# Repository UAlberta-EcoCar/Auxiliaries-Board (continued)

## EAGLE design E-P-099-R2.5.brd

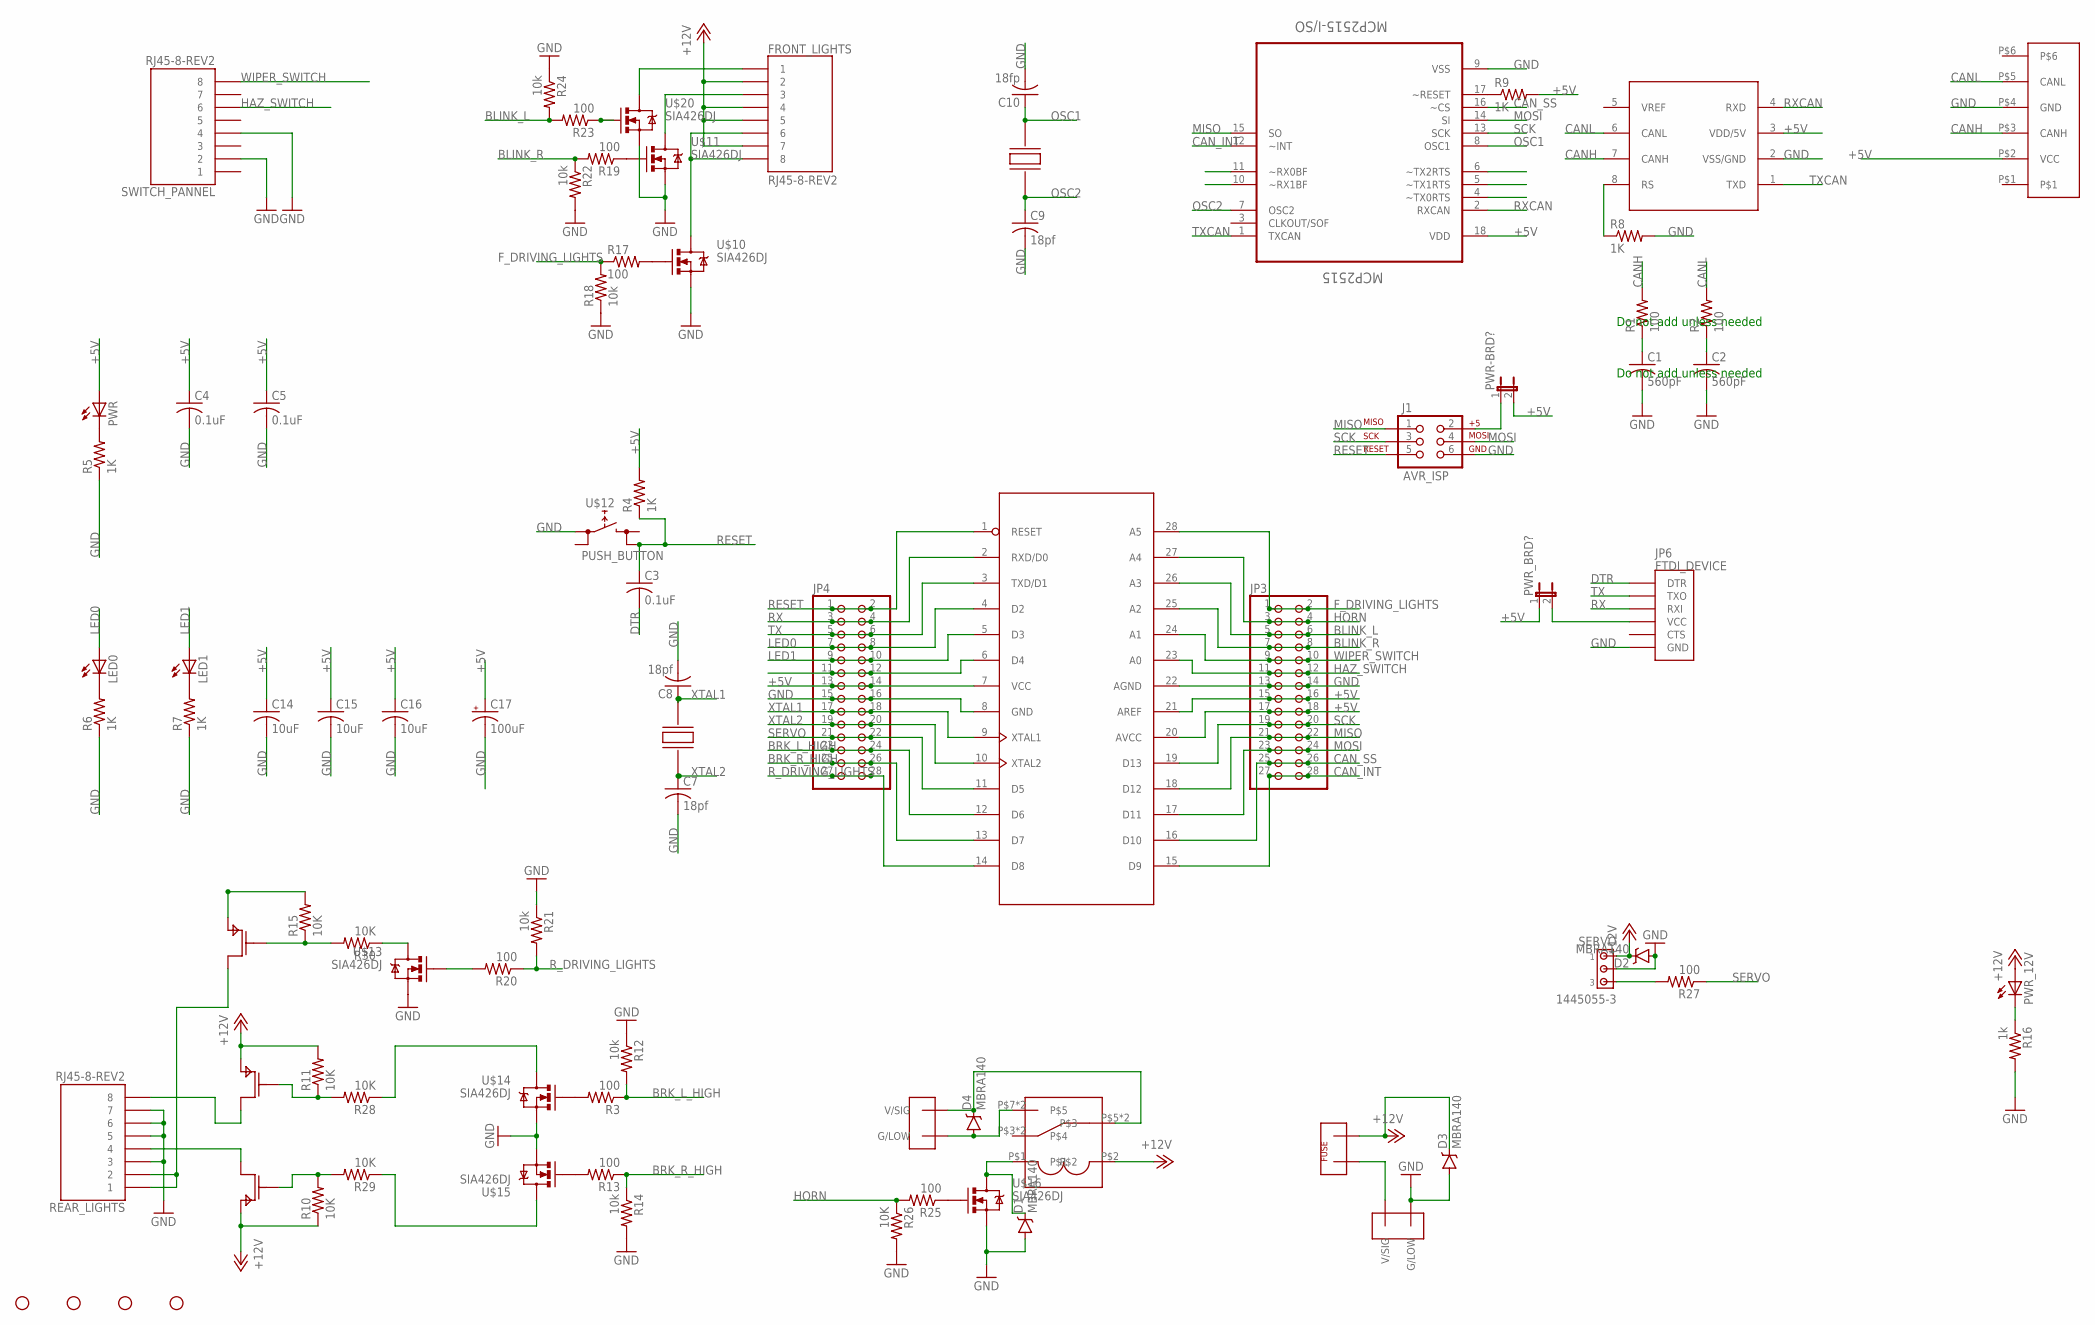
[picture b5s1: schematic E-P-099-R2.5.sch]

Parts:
C1, C2: 560pF; C0805
C3, C4, C5: 0.1uF; C0805
C7, C8, C9: 18pf; C0805
C10: 18fp; C0805
C14, C15, C16: 10uF; C0805
C17: 100uF; PANASONIC_D
CAN-BUS: CAN_6P6C
D1, D2, D3, D4: MBRA140; SMA-DIODE
FRONT_LIGHTS: RJ45-8-REV2; RJ45-8
HORN: TE770966; 2X1-MATE-N-LOCK
J1: AVR_ISP; 2X3
JP3, JP4: PINHD-2X14; 2X14
JP6: FTDI_DEVICE; FTDI_DEVICE_SIDE
LED0, LED1: LED1206; LED-1206
MCP2515: MCP2515-I/SO; SOIC127P1034X264-18N
PWR: LED1206; LED-1206
PWR-BRD?: JP1E; JP1
PWR_12V: LEDCHIPLED_1206; CHIPLED_1206
PWR_BRD?: JP1E; JP1
R1, R2, R3, R13, R17, R19, R20, R23, R25, R27: 100; M0805
R4, R5, R6, R7, R8, R9: 1K; M0805
R10, R11, R15, R26, R28, R29, R30: 10K; M0805
R12, R14, R18, R21, R22, R24: 10k; M0805
R16: 1k; M0805
REAR_LIGHTS: RJ45-8-REV2; RJ45-8
SERVO: 1445055-3
STANDOFF1, STANDOFF2, STANDOFF3, STANDOFF4: STAND-OFF
SWITCH_PANNEL: RJ45-8-REV2; RJ45-8
U$2: MCP2551DIP; DIP8
U$3, U$5, U$6: SIA449DJ; SIA449DJ-T1-GE3CT-ND
U$4: ATMEGA328; DIP28-0.3IN
U$7: RELAY; RTD34012
U$8: TE770966; 2X1-MATE-N-LOCK
U$9: FUSEMINI-BLADE; MINI-BLADE-FUSE
U$10, U$11, U$13, U$14, U$15, U$16, U$20: SIA426DJ; SC70-6L
U$12: PUSH_BUTTON; PUSHBUTTON
U$18, U$19: CRYSTAL; 7A_CRYSTAL

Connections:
+5V: C4.1, C5.1, C14.1, C15.1, C16.1, C17.+, CAN-BUS.P$2 (VCC), JP3.15, JP3.16, JP3.17, JP3.18, JP4.13, JP4.14, MCP2515.18 (VDD), PWR.A, PWR-BRD?.2, PWR_BRD?.1, R4.2, R9.2, U$2.3 (VDD/5V), U$4.7 (VCC), U$4.20 (AVCC), U$4.21 (AREF)
+12V: D2.C, D3.C, FRONT_LIGHTS.2, FRONT_LIGHTS.4, FRONT_LIGHTS.5, FRONT_LIGHTS.7, PWR_12V.A, R10.1, R11.2, R15.2, SERVO.1, U$3.P$4 (P$S), U$3.P$5 (P$S), U$5.P$4 (P$S), U$5.P$5 (P$S), U$6.P$4 (P$S), U$6.P$5 (P$S), U$7.P$2, U$9.OUT
BLINK_L: JP3.5, JP3.6, R23.2, R24.2, U$4.26 (A3)
BLINK_R: JP3.7, JP3.8, R19.2, R22.1, U$4.25 (A2)
BRK_L_HIGH: JP4.23, JP4.24, R3.1, R12.2, U$4.12 (D6)
BRK_R_HIGH: JP4.25, JP4.26, R13.1, R14.1, U$4.13 (D7)
CANH: CAN-BUS.P$3 (CANH), R1.2, U$2.7 (CANH)
CANL: CAN-BUS.P$5 (CANL), R2.2, U$2.6 (CANL)
CAN_INT: JP3.27, JP3.28, MCP2515.12 (~INT), U$4.15 (D9)
CAN_SS: JP3.25, JP3.26, MCP2515.16 (~CS), U$4.16 (D10)
DTR: C3.2, JP6.P$1 (DTR)
F_DRIVING_LIGHTS: JP3.1, JP3.2, R17.1, R18.2, U$4.28 (A5)
GND: C1.2, C2.2, C4.2, C5.2, C7.2, C8.2, C9.2, C10.2, C14.2, C15.2, C16.2, C17.-, CAN-BUS.P$4 (GND), D1.A, D2.A, D3.A, J1.6, JP3.13, JP3.14, JP4.15, JP4.16, JP6.P$6 (GND), MCP2515.9 (VSS), R5.1, R6.1, R7.1, R8.2, R12.1, R14.2, R16.2, R18.1, R21.1, R22.2, R24.1, R26.2, REAR_LIGHTS.3, REAR_LIGHTS.5, REAR_LIGHTS.6, REAR_LIGHTS.7, SERVO.2, SWITCH_PANNEL.2, SWITCH_PANNEL.4, U$2.2 (VSS/GND), U$4.8 (GND), U$4.22 (AGND), U$8.CIRCUIT2 (G/LOW), U$10.S@0 (S), U$10.S@1 (S), U$11.S@0 (S), U$11.S@1 (S), U$12.L1 (L), U$13.S@0 (S), U$13.S@1 (S), U$14.S@0 (S), U$14.S@1 (S), U$15.S@0 (S), U$15.S@1 (S), U$16.S@0 (S), U$16.S@1 (S), U$20.S@0 (S), U$20.S@1 (S)
HAZ_SWITCH: JP3.11, JP3.12, SWITCH_PANNEL.6, U$4.23 (A0)
HORN: JP3.3, JP3.4, R25.2, R26.1, U$4.27 (A4)
LED0: JP4.7, JP4.8, LED0.A, U$4.4 (D2)
LED1: JP4.9, JP4.10, LED1.A, U$4.5 (D3)
MISO: J1.1, JP3.21, JP3.22, MCP2515.15 (SO), U$4.18 (D12)
MOSI: J1.4, JP3.23, JP3.24, MCP2515.14 (SI), U$4.17 (D11)
unnamed: REAR_LIGHTS.4, U$6.P$1 (P$D)
unnamed: REAR_LIGHTS.8, U$5.P$1 (P$D)
unnamed: R13.2, U$15.G
unnamed: R20.2, U$13.G
unnamed: JP6.P$4 (VCC), PWR_BRD?.2
unnamed: LED0.C, R6.2
unnamed: LED1.C, R7.2
unnamed: R8.1, U$2.8 (RS)
unnamed: REAR_LIGHTS.1, REAR_LIGHTS.2, U$3.P$1 (P$D)
unnamed: R11.1, R28.2, U$5.P$6 (P$G)
unnamed: MCP2515.17 (~RESET), R9.1
unnamed: PWR_12V.C, R16.1
unnamed: R23.1, U$20.G
unnamed: D4.C, HORN.CIRCUIT1 (V/SIG), U$7.P$5, U$7.P$6
unnamed: PWR.C, R5.2
unnamed: FRONT_LIGHTS.1, U$20.D
unnamed: R3.2, U$14.G
unnamed: R15.1, R30.2, U$3.P$6 (P$G)
unnamed: FRONT_LIGHTS.3, U$11.D
unnamed: C1.1, R1.1
unnamed: C2.1, R2.1
unnamed: FRONT_LIGHTS.6, FRONT_LIGHTS.8, U$10.D
unnamed: D4.A, HORN.CIRCUIT2 (G/LOW), U$7.P$7, U$7.P$8
unnamed: R25.1, U$16.G
unnamed: D1.C, U$7.P$1, U$16.D
unnamed: R10.2, R29.2, U$6.P$6 (P$G)
unnamed: R19.1, U$11.G
unnamed: R30.1, U$13.D
unnamed: R17.2, U$10.G
unnamed: R27.2, SERVO.3
unnamed: J1.2, PWR-BRD?.1
unnamed: JP4.11, JP4.12, U$4.6 (D4)
unnamed: R28.1, U$14.D
unnamed: R29.1, U$15.D
unnamed: U$8.CIRCUIT1 (V/SIG), U$9.IN
OSC1: C10.1, MCP2515.8 (OSC1), U$19.P$2
OSC2: C9.1, MCP2515.7 (OSC2), U$19.P$1
RESET: C3.1, J1.5, JP4.1, JP4.2, R4.1, U$4.1 (RESET), U$12.R2 (R)
RX: JP4.3, JP4.4, JP6.P$3 (RXI), U$4.2 (RXD/D0)
RXCAN: MCP2515.2 (RXCAN), U$2.4 (RXD)
R_DRIVING_LIGHTS: JP4.27, JP4.28, R20.1, R21.2, U$4.14 (D8)
SCK: J1.3, JP3.19, JP3.20, MCP2515.13 (SCK), U$4.19 (D13)
SERVO: JP4.21, JP4.22, R27.1, U$4.11 (D5)
TX: JP4.5, JP4.6, JP6.P$2 (TXO), U$4.3 (TXD/D1)
TXCAN: MCP2515.1 (TXCAN), U$2.1 (TXD)
WIPER_SWITCH: JP3.9, JP3.10, SWITCH_PANNEL.8, U$4.24 (A1)
XTAL1: C8.1, JP4.17, JP4.18, U$4.9 (XTAL1), U$18.P$2
XTAL2: C7.1, JP4.19, JP4.20, U$4.10 (XTAL2), U$18.P$1

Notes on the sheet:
Do not add unless needed

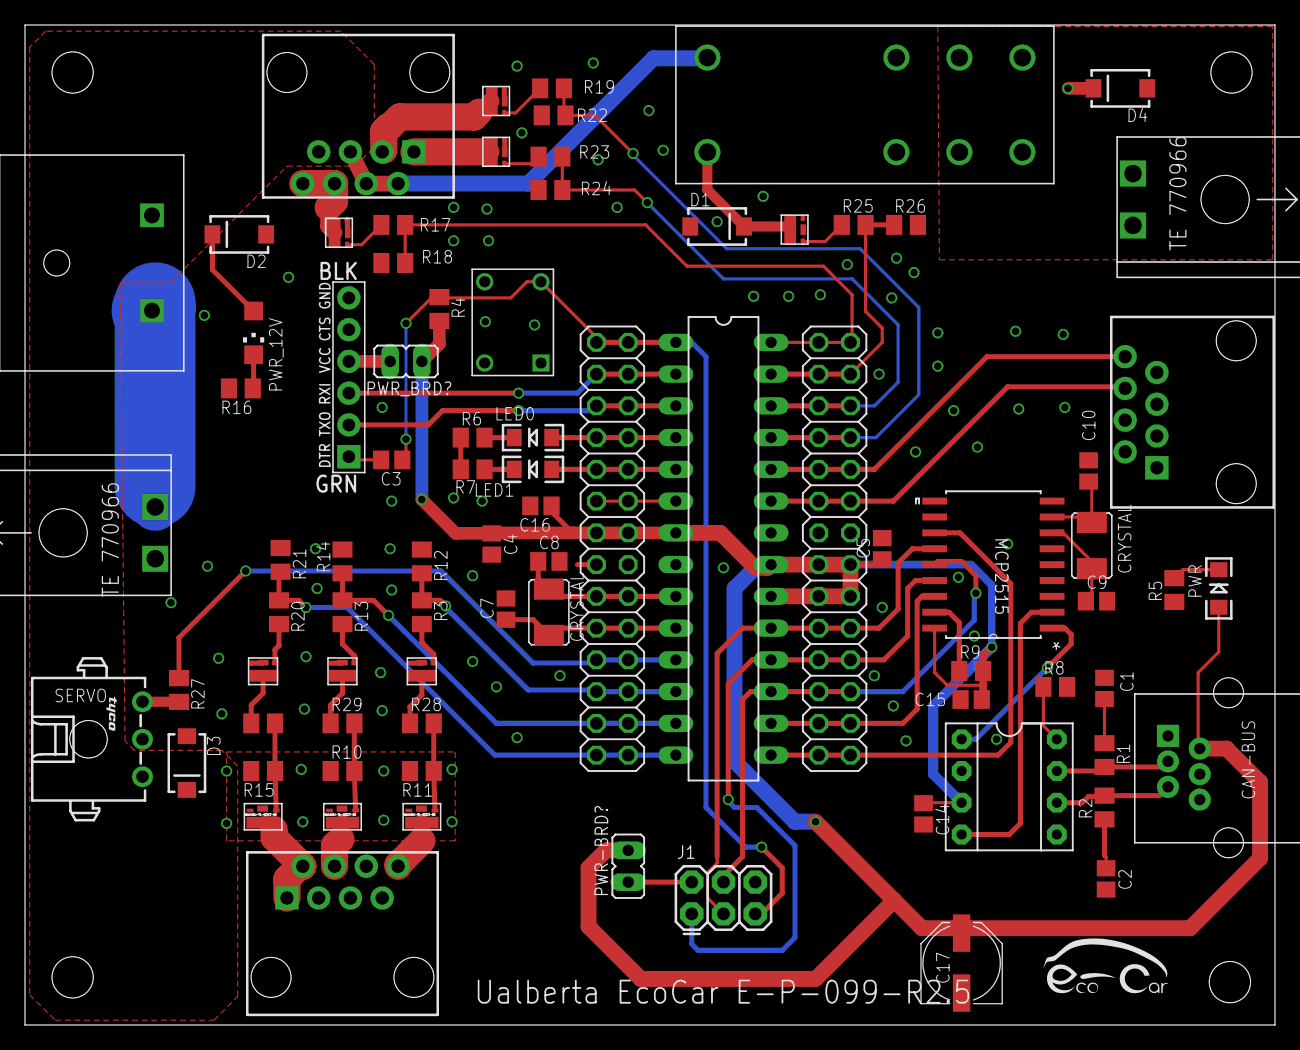
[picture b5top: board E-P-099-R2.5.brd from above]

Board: 2 copper layers, 100.0 x 80.0 mm, 86 parts (0 on the bottom side), 67 nets.

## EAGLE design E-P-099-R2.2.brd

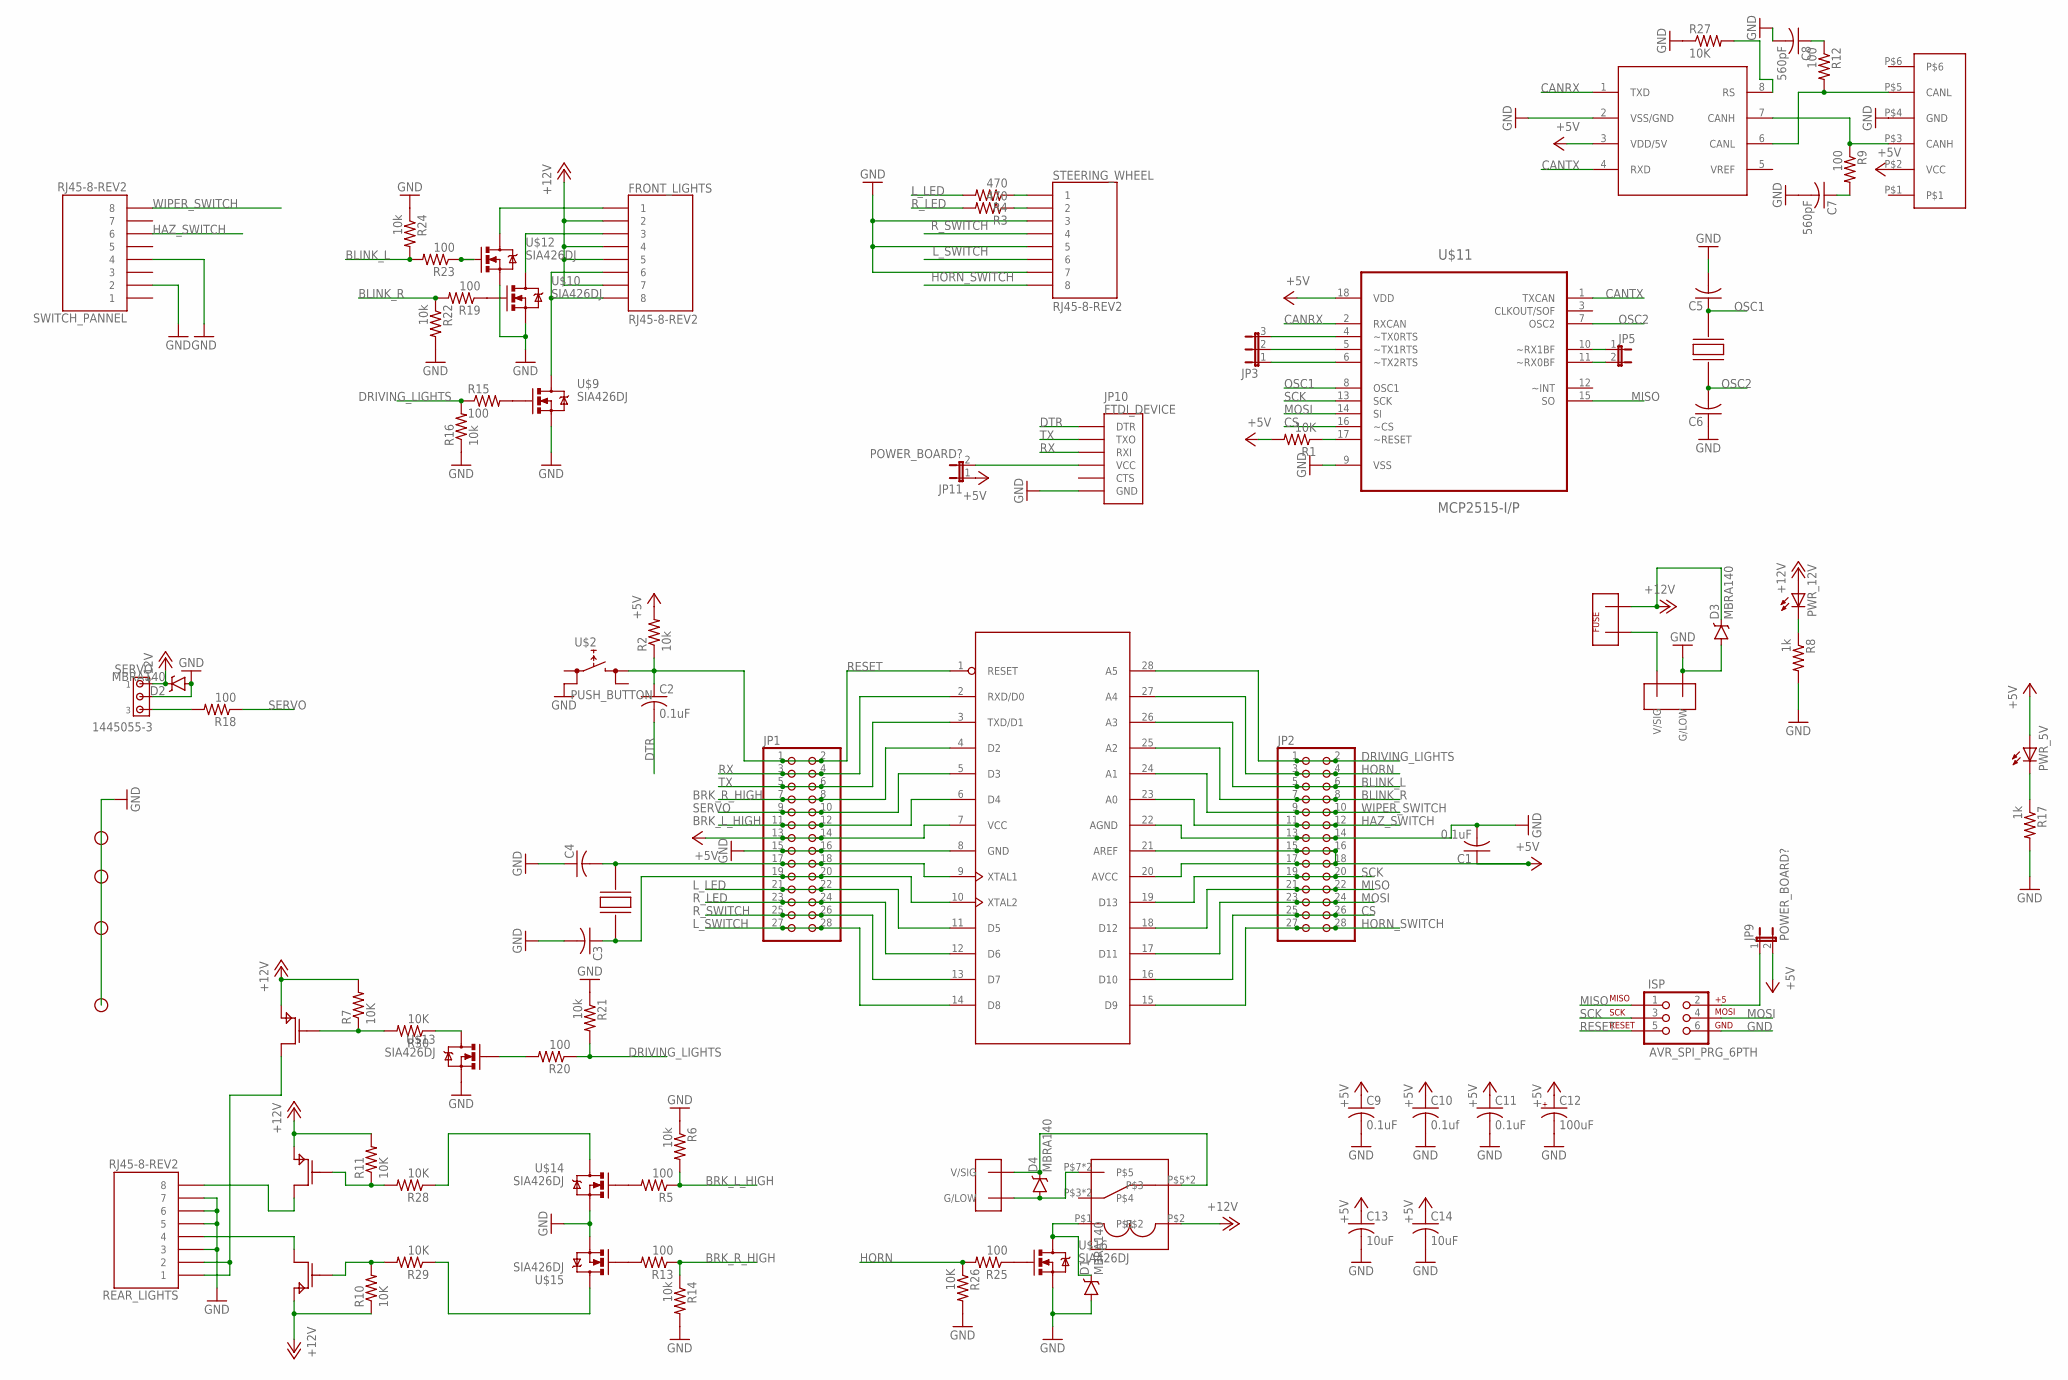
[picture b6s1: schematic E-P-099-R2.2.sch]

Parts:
C1, C2, C9, C11: 0.1uF; C0805
C3, C4, C5, C6: C-USC0805; C0805
C7, C8: 560pF; C0805
C10: 0.1uf; C0805
C12: 100uF; PANASONIC_C
C13, C14: 10uF; C0805
CAN_BUS: CAN_6P6C
D1, D2, D3, D4: MBRA140; SMA-DIODE
FRONT_LIGHTS: RJ45-8-REV2; RJ45-8
HORN: TE770966; 2X1-MATE-N-LOCK
ISP: AVR_SPI_PRG_6PTH; 2X3
JP1, JP2: PINHD-2X14; 2X14
JP3: JP2E; JP2
JP4, JP6, JP7, JP8: STAND-OFF
JP5: JP1E; JP1
JP9, JP11: POWER_BOARD?; 1X02
JP10: FTDI_DEVICE; FTDI_DEVICE_SIDE
PWR_5V, PWR_12V: LEDCHIPLED_1206; CHIPLED_1206
R1, R7, R10, R11, R26, R27, R28, R29, R30: 10K; M0805
R2, R6, R14, R16, R21, R22, R24: 10k; M0805
R3, R4: 470; M0805
R5, R9, R12, R13, R15, R18, R19, R20, R23, R25: 100; M0805
R8, R17: 1k; M0805
REAR_LIGHTS: RJ45-8-REV2; RJ45-8
SERVO: 1445055-3
STEERING_WHEEL: RJ45-8-REV2; RJ45-8
SWITCH_PANNEL: RJ45-8-REV2; RJ45-8
U$1: ATMEGA328; DIP28-0.3IN
U$2: PUSH_BUTTON; PUSHBUTTON
U$3: MCP2551DIP; DIP8
U$4, U$6: CRYSTAL; 7A_CRYSTAL
U$5: TE770966; 2X1-MATE-N-LOCK
U$7: RELAY; RTD34012
U$8: FUSEMINI-BLADE; MINI-BLADE-FUSE
U$9, U$10, U$12, U$13, U$14, U$15, U$16: SIA426DJ; SC70-6L
U$11: MCP2515-I/P; DIP254P762X432-18
U$17, U$18, U$19: SIA449DJ; SIA449DJ-T1-GE3CT-ND

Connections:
+5V: C1.1, C9.1, C10.1, C11.1, C12.+, C13.1, C14.1, CAN_BUS.P$2 (VCC), JP1.13, JP1.14, JP2.15, JP2.16, JP2.17, JP2.18, JP9.2, JP11.1, PWR_5V.A, R1.2, R2.2, U$1.7 (VCC), U$1.20 (AVCC), U$1.21 (AREF), U$3.3 (VDD/5V), U$11.18 (VDD)
+12V: D2.C, D3.C, FRONT_LIGHTS.2, FRONT_LIGHTS.4, FRONT_LIGHTS.5, FRONT_LIGHTS.7, PWR_12V.A, R7.2, R10.1, R11.2, SERVO.1, U$7.P$2, U$8.OUT, U$17.P$5 (P$S), U$17.P$6 (P$S), U$18.P$5 (P$S), U$18.P$6 (P$S), U$19.P$5 (P$S), U$19.P$6 (P$S)
BLINK_L: JP2.5, JP2.6, R23.2, R24.2, U$1.26 (A3)
BLINK_R: JP2.7, JP2.8, R19.2, R22.1, U$1.25 (A2)
BRK_L_HIGH: JP1.11, JP1.12, R5.1, R6.2, U$1.6 (D4)
BRK_R_HIGH: JP1.7, JP1.8, R13.1, R14.1, U$1.4 (D2)
CANRX: U$3.1 (TXD), U$11.2 (RXCAN)
CANTX: U$3.4 (RXD), U$11.1 (TXCAN)
CS: JP2.25, JP2.26, U$1.16 (D10), U$11.16 (~CS)
DRIVING_LIGHTS: JP2.1, JP2.2, R15.1, R16.2, R20.1, R21.2, U$1.28 (A5)
DTR: C2.2, JP10.P$1 (DTR)
GND: C1.2, C3.2, C4.1, C5.2, C6.1, C7.2, C8.2, C9.2, C10.2, C11.2, C12.-, C13.2, C14.2, CAN_BUS.P$4 (GND), D1.A, D2.A, D3.A, ISP.6, JP1.15, JP1.16, JP2.13, JP2.14, JP10.P$6 (GND), R6.1, R8.2, R14.2, R16.1, R17.2, R21.1, R22.2, R24.1, R26.2, R27.1, REAR_LIGHTS.3, REAR_LIGHTS.5, REAR_LIGHTS.6, REAR_LIGHTS.7, SERVO.2, STEERING_WHEEL.3, STEERING_WHEEL.5, STEERING_WHEEL.7, SWITCH_PANNEL.2, SWITCH_PANNEL.4, U$1.8 (GND), U$1.22 (AGND), U$2.L2 (L), U$3.2 (VSS/GND), U$5.CIRCUIT2 (G/LOW), U$9.S@0 (S), U$9.S@1 (S), U$10.S@0 (S), U$10.S@1 (S), U$11.9 (VSS), U$12.S@0 (S), U$12.S@1 (S), U$13.S@0 (S), U$13.S@1 (S), U$14.S@0 (S), U$14.S@1 (S), U$15.S@0 (S), U$15.S@1 (S), U$16.S@0 (S), U$16.S@1 (S)
HAZ_SWITCH: JP2.11, JP2.12, SWITCH_PANNEL.6, U$1.23 (A0)
HORN: JP2.3, JP2.4, R25.2, R26.1, U$1.27 (A4)
HORN_SWITCH: JP2.27, JP2.28, STEERING_WHEEL.8, U$1.15 (D9)
L_LED: JP1.21, JP1.22, R4.2, U$1.11 (D5)
L_SWITCH: JP1.27, JP1.28, STEERING_WHEEL.6, U$1.14 (D8)
MISO: ISP.1, JP2.21, JP2.22, U$1.18 (D12), U$11.15 (SO)
MOSI: ISP.4, JP2.23, JP2.24, U$1.17 (D11), U$11.14 (SI)
unnamed: CAN_BUS.P$3 (CANH), R9.1, U$3.7 (CANH)
unnamed: PWR_12V.C, R8.1
unnamed: REAR_LIGHTS.4, U$19.P$1 (P$D)
unnamed: C8.1, R12.1
unnamed: ISP.2, JP9.1
unnamed: C7.1, R9.2
unnamed: R13.2, U$15.G
unnamed: FRONT_LIGHTS.1, U$12.D
unnamed: CAN_BUS.P$5 (CANL), R12.2, U$3.6 (CANL)
unnamed: REAR_LIGHTS.1, REAR_LIGHTS.2, U$17.P$1 (P$D)
unnamed: C3.1, JP1.19, JP1.20, U$1.10 (XTAL2), U$4.P$1
unnamed: R3.1, STEERING_WHEEL.2
unnamed: R4.1, STEERING_WHEEL.1
unnamed: FRONT_LIGHTS.3, U$10.D
unnamed: R18.2, SERVO.3
unnamed: R15.2, U$9.G
unnamed: FRONT_LIGHTS.6, FRONT_LIGHTS.8, U$9.D
unnamed: D4.C, HORN.CIRCUIT1 (V/SIG), U$7.P$5, U$7.P$6
unnamed: C4.2, JP1.17, JP1.18, U$1.9 (XTAL1), U$4.P$2
unnamed: JP3.3, U$11.4 (~TX0RTS)
unnamed: R5.2, U$14.G
unnamed: R7.1, R30.2, U$17.P$4 (P$G)
unnamed: JP10.P$4 (VCC), JP11.2
unnamed: R20.2, U$13.G
unnamed: REAR_LIGHTS.8, U$18.P$1 (P$D)
unnamed: R27.2, U$3.8 (RS)
unnamed: R1.1, U$11.17 (~RESET)
unnamed: D4.A, HORN.CIRCUIT2 (G/LOW), U$7.P$7, U$7.P$8
unnamed: R25.1, U$16.G
unnamed: D1.C, U$7.P$1, U$16.D
unnamed: R11.1, R28.2, U$18.P$4 (P$G)
unnamed: R10.2, R29.2, U$19.P$4 (P$G)
unnamed: R19.1, U$10.G
unnamed: R30.1, U$13.D
unnamed: R23.1, U$12.G
unnamed: PWR_5V.C, R17.1
unnamed: R28.1, U$14.D
unnamed: R29.1, U$15.D
unnamed: U$5.CIRCUIT1 (V/SIG), U$8.IN
unnamed: JP3.2, U$11.5 (~TX1RTS)
unnamed: JP3.1, U$11.6 (~TX2RTS)
unnamed: JP5.1, U$11.10 (~RX1BF)
unnamed: JP5.2, U$11.11 (~RX0BF)
OSC1: C5.1, U$6.P$2, U$11.8 (OSC1)
OSC2: C6.2, U$6.P$1, U$11.7 (OSC2)
RESET: C2.1, ISP.5, JP1.1, JP1.2, R2.1, U$1.1 (RESET), U$2.R1 (R)
RX: JP1.3, JP1.4, JP10.P$3 (RXI), U$1.2 (RXD/D0)
R_LED: JP1.23, JP1.24, R3.2, U$1.12 (D6)
R_SWITCH: JP1.25, JP1.26, STEERING_WHEEL.4, U$1.13 (D7)
SCK: ISP.3, JP2.19, JP2.20, U$1.19 (D13), U$11.13 (SCK)
SERVO: JP1.9, JP1.10, R18.1, U$1.5 (D3)
TX: JP1.5, JP1.6, JP10.P$2 (TXO), U$1.3 (TXD/D1)
WIPER_SWITCH: JP2.9, JP2.10, SWITCH_PANNEL.8, U$1.24 (A1)

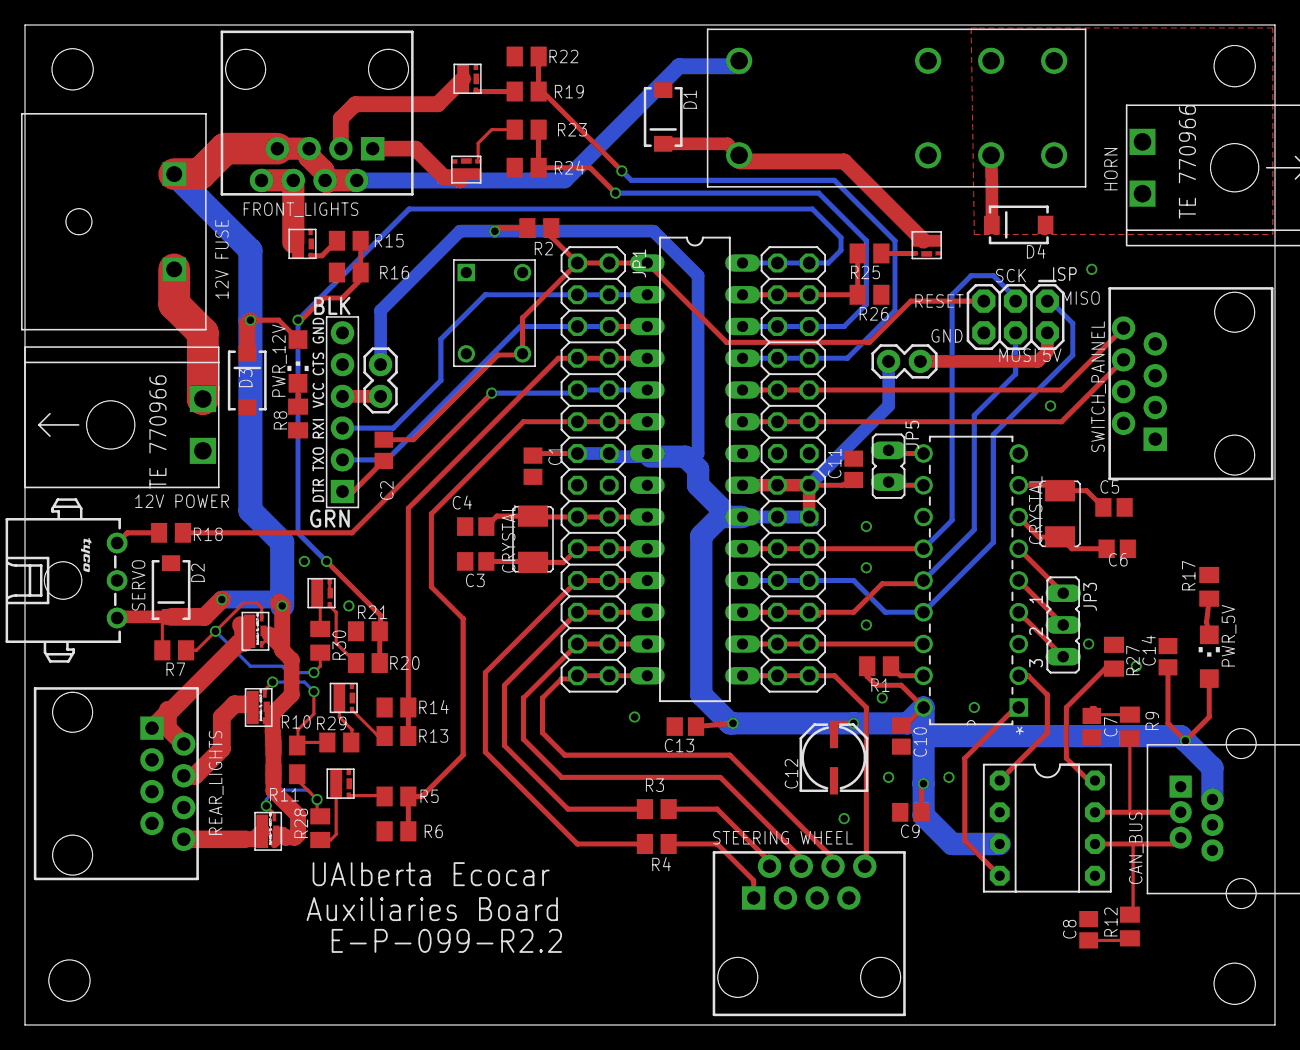
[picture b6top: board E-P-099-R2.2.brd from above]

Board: 2 copper layers, 100.0 x 80.0 mm, 88 parts (0 on the bottom side), 72 nets.

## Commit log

2016-01-23 added eagle files
2016-03-04 Added most recent revision
2017-01-29 version 2.6
2017-09-17 design fixes
    added LED's to all signals and fixed up some layout issues
2017-09-17 removed old version
    deleted R2.6 for R2.7
2017-09-17 archived 2.6
    I forgot to do this before making changes.. really just here for posterity sake.
2017-10-02 new Aux design
    Changed 5V input from Rj11 to pin connector, changed servo power to 5V onboard. cleaned up routing and silkscreen for easier soldering. needs new logo.
2017-10-10 Gerbers Generated
2017-10-16 pinouts updated to match new light boards
    New changes to the pinouts for the ethernet connectors to match the new design of the head and tail light boards. Also designed to be symmetric across the connector to prevent mistakes.
2017-11-25 Revert "pinouts updated to match new light boards"
    This reverts commit c6705fe930e627c4a8d5c034fe7450b97c4f4bb6.
2017-11-27 Deleted Gerbers and added horn board
2017-11-27 Added Connectors to horn board
2017-12-03 Uploading new revision
2018-05-06 VER.3
    Added through hole mosfets, fixed input switch logic, improved pull downs on inout, added connector for break switch, increased board size and fixed routing,
2018-05-13 added pull down resistors to switches, added windshield wiper switch, added capacitors to make mike happy, adjusted led circuit on outputs might need different resistor values, changed a couple other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
2018-05-23 added separate power for servo, cleaned up a bit of board layout, remade some missing eagle libraries and added them to library repo
2018-05-23 added silk screen labels to some parts. moved back to coordinate system origin
2018-05-29 took some signals off of steering wheel and put on new ethernet
